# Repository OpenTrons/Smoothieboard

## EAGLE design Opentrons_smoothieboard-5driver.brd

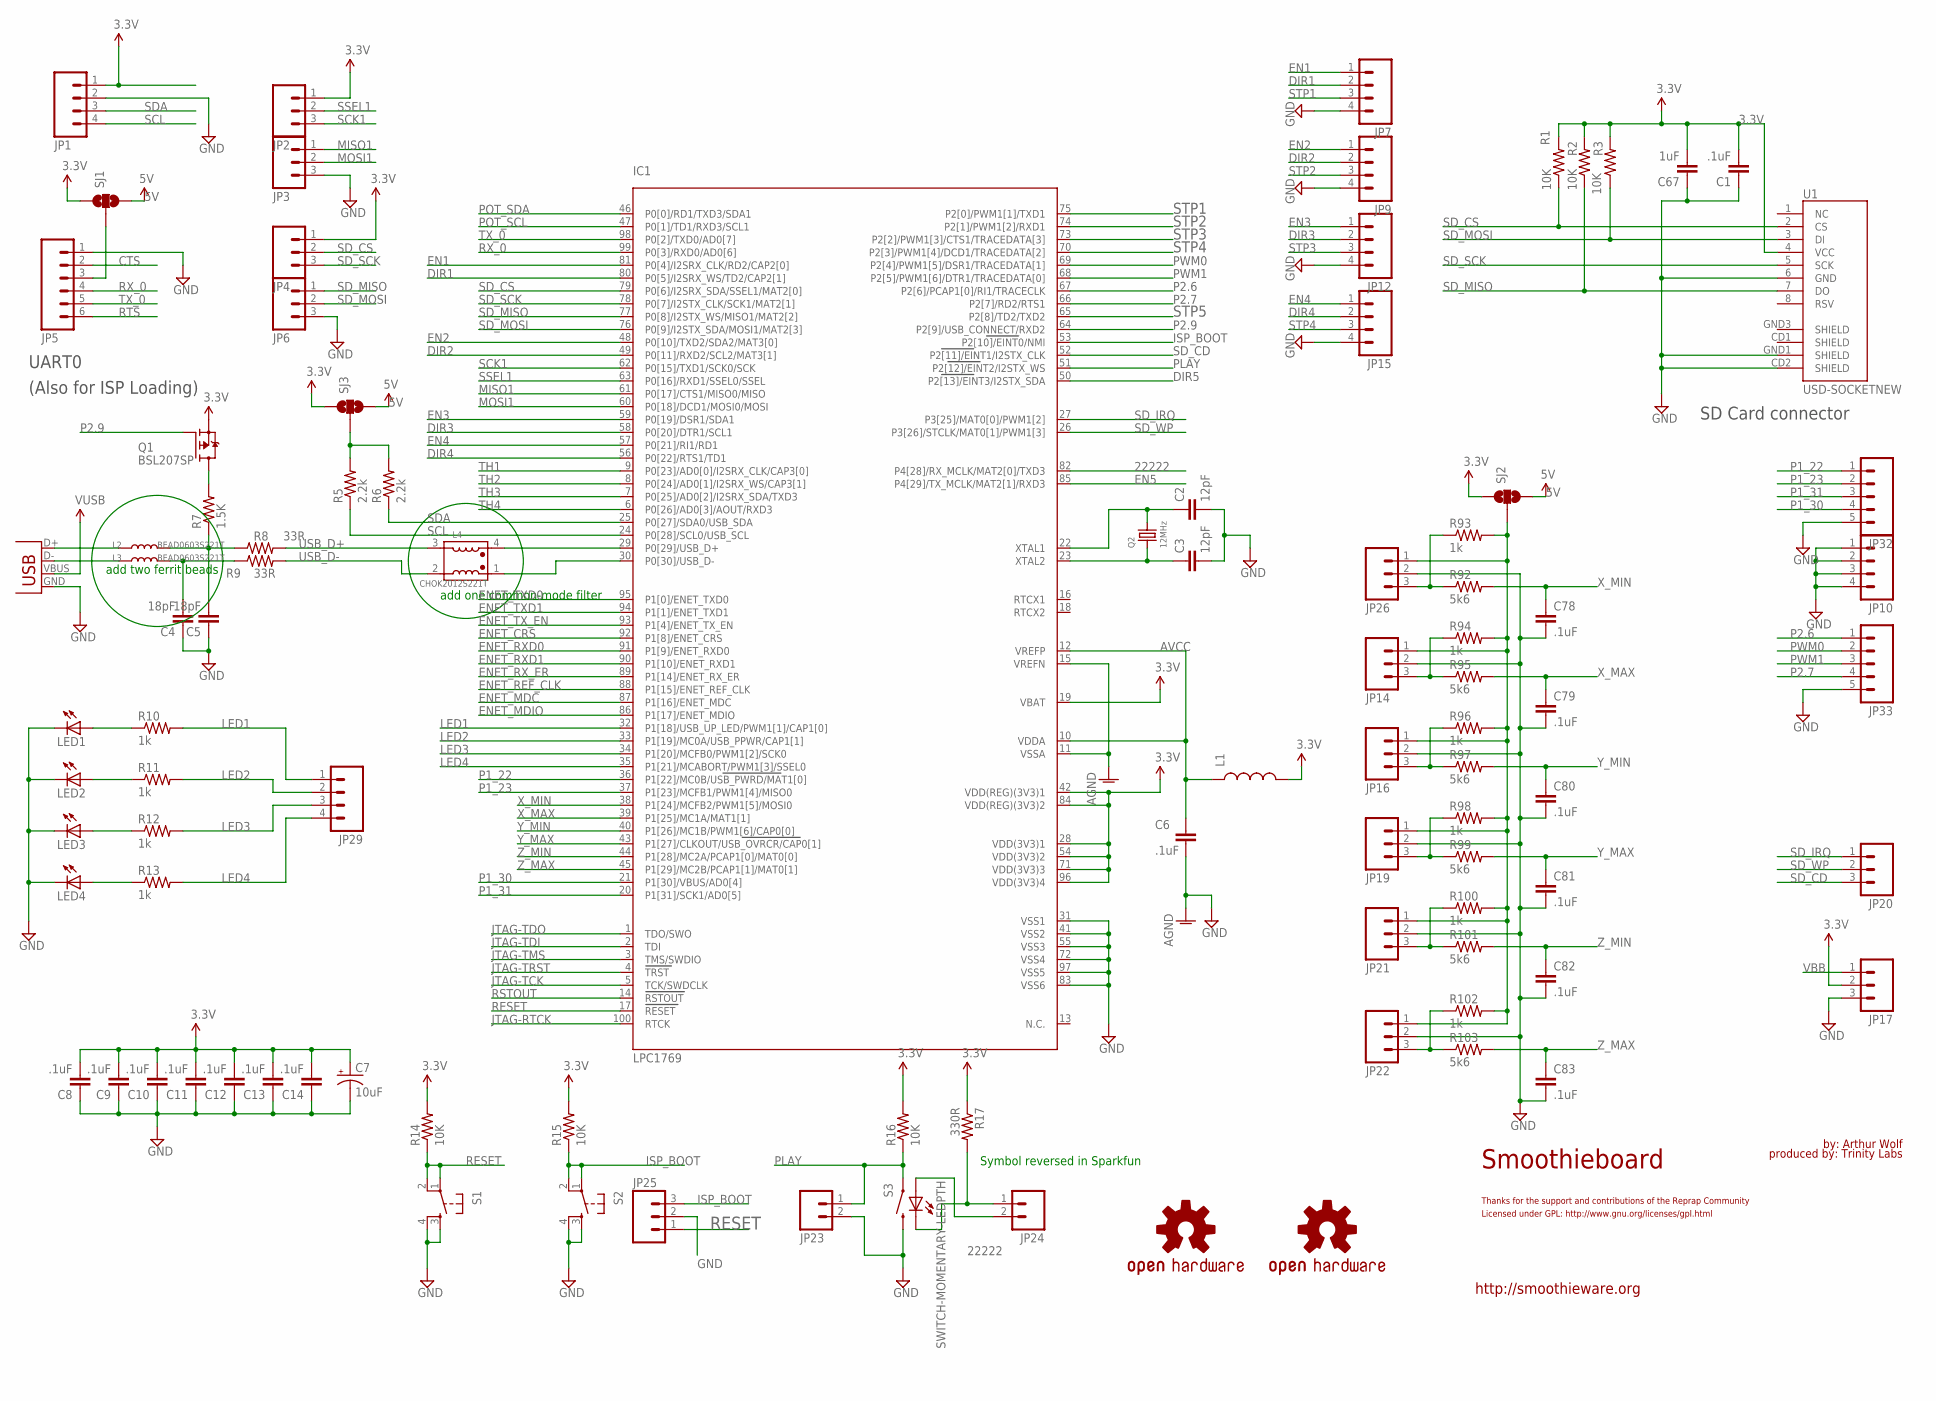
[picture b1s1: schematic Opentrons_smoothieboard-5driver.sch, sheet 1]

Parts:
C1, C6, C8, C9, C10, C11, C12, C13, C14, C78, C79, C80, C81, C82, C83: .1uF; C0603
C2, C3: 12pF; C0603
C4, C5: 18pF; C0603
C7: 10uF; EIA3216
C67: 1uF; C0805
IC1: LPC1769; LQFP100
JP1, JP7, JP9, JP10, JP12, JP15, JP29: M041X04_NO_SILK; 1X04_NO_SILK
JP2, JP3, JP4, JP6: M031X03_NO_SILK; 1X03_NO_SILK
JP5: M06POLAR; MOLEX-1X6
JP14, JP16, JP19, JP21, JP22, JP26: M03POLAR; MOLEX-1X3
JP17, JP20, JP25: M03PTH; 1X03
JP23, JP24: M02PTH; 1X02
JP32, JP33: M05PTH; 1X05
L1: INDUCTOR0603; 0603
L2, L3: BEAD0603S221T; 0603(1608)
L4: CHOK2012S221T; L-2012
LED1, LED2, LED3, LED4: LEDCHIP-LED0805; CHIP-LED0805
Q1: BSL207SP; SC74_INFINEON
Q2: 12MHz; CRYSTAL_3.2X2.5
R1, R2, R3, R14, R15, R16: 10K; R0603
R5, R6: 2.2k; R0603
R7: 1.5K; R0603
R8, R9: 33R; R0603
R10, R11, R12, R13, R93, R94, R96, R98, R100, R102: 1k; R0603
R17: 330R; R0603
R92, R95, R97, R99, R101, R103: 5k6; R0603
S1, S2: TAC_SWITCHSMD; TACTILE_SWITCH_SMD
S3: SWITCH-MOMENTARY-LEDPTH; TACTILE-PTH-LED-12MM
SJ1, SJ2, SJ3: SOLDERJUMPER_2WAYS; SJ_3
U1: USD-SOCKETNEW; MICRO-SD-SOCKET-PP
U$8, U$9: OSHW-LOGOH; OSHW-LOGO-HUGE
X14: USBPTH; USB-B-PTH

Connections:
3.3V: C1.2, C7.A (+), C8.2, C9.2, C10.2, C11.2, C12.2, C13.2, C14.2, C67.2, IC1.19 (VBAT), IC1.28 (VDD(3V3)1), IC1.42 (VDD(REG)(3V3)1), IC1.54 (VDD(3V3)2), IC1.71 (VDD(3V3)3), IC1.84 (VDD(REG)(3V3)2), IC1.96 (VDD(3V3)4), JP1.1, JP2.1, JP4.1, JP17.2, L1.2, Q1.4 (S), R1.2, R2.2, R3.2, R14.2, R15.2, R16.2, R17.1, SJ1.1, SJ2.1, SJ3.1, U1.4 (VCC); also elsewhere on the board
5V: SJ1.3, SJ2.3, SJ3.3; also elsewhere on the board
22222: IC1.82 (P4[28]/RX_MCLK/MAT2[0]/TXD3), JP24.2, S3.A
AGND: C6.2, IC1.11 (VSSA), IC1.15 (VREFN); also elsewhere on the board
AVCC: C6.1, IC1.10 (VDDA), IC1.12 (VREFP), L1.1; also elsewhere on the board
CTS: JP5.2
DIR1: IC1.80 (P0[5]/I2SRX_WS/TD2/CAP2[1]), JP7.2; also elsewhere on the board
DIR2: IC1.49 (P0[11]/RXD2/SCL2/MAT3[1]), JP9.2; also elsewhere on the board
DIR3: IC1.58 (P0[20]/DTR1/SCL1), JP12.2; also elsewhere on the board
DIR4: IC1.56 (P0[22]/RTS1/TD1), JP15.2; also elsewhere on the board
DIR5: IC1.50 (P2[13]/EINT3/I2STX_SDA); also elsewhere on the board
EN1: IC1.81 (P0[4]/I2SRX_CLK/RD2/CAP2[0]), JP7.1; also elsewhere on the board
EN2: IC1.48 (P0[10]/TXD2/SDA2/MAT3[0]), JP9.1; also elsewhere on the board
EN3: IC1.59 (P0[19]/DSR1/SDA1), JP12.1; also elsewhere on the board
EN4: IC1.57 (P0[21]/RI1/RD1), JP15.1; also elsewhere on the board
EN5: IC1.85 (P4[29]/TX_MCLK/MAT2[1]/RXD3); also elsewhere on the board
ENET_CRS: IC1.92 (P1[8]/ENET_CRS); also elsewhere on the board
ENET_MDC: IC1.87 (P1[16]/ENET_MDC); also elsewhere on the board
ENET_MDIO: IC1.86 (P1[17]/ENET_MDIO); also elsewhere on the board
ENET_REF_CLK: IC1.88 (P1[15]/ENET_REF_CLK); also elsewhere on the board
ENET_RXD0: IC1.91 (P1[9]/ENET_RXD0); also elsewhere on the board
ENET_RXD1: IC1.90 (P1[10]/ENET_RXD1); also elsewhere on the board
ENET_RX_ER: IC1.89 (P1[14]/ENET_RX_ER); also elsewhere on the board
ENET_TXD0: IC1.95 (P1[0]/ENET_TXD0); also elsewhere on the board
ENET_TXD1: IC1.94 (P1[1]/ENET_TXD1); also elsewhere on the board
ENET_TX_EN: IC1.93 (P1[4]/ENET_TX_EN); also elsewhere on the board
GND: C1.1, C2.2, C3.2, C4.1, C5.1, C7.C (-), C8.1, C9.1, C10.1, C11.1, C12.1, C13.1, C14.1, C67.1, C78.2, C79.2, C80.2, C81.2, C82.2, C83.2, IC1.31 (VSS1), IC1.41 (VSS2), IC1.55 (VSS3), IC1.72 (VSS4), IC1.83 (VSS6), IC1.97 (VSS5), JP1.2, JP3.3, JP5.1, JP6.3, JP7.4, JP9.4, JP10.1, JP10.2, JP10.3, JP10.4, JP12.4, JP14.2, JP15.4, JP16.2, JP17.3, JP19.2, JP21.2, JP22.2, JP23.2, JP25.2, JP26.2, JP32.5, JP33.5, LED1.C, LED2.C, LED3.C, LED4.C, S1.3, S1.4, S2.3, S2.4, S3.2, U1.6 (GND), U1.CD2 (SHIELD), U1.GND1 (SHIELD), X14.GND; also elsewhere on the board
ISP_BOOT: IC1.53 (P2[10]/EINT0/NMI), JP25.3, R15.1, S2.1, S2.2
JTAG-RTCK: IC1.100 (RTCK)
JTAG-TCK: IC1.5 (TCK/SWDCLK)
JTAG-TDI: IC1.2 (TDI)
JTAG-TDO: IC1.1 (TDO/SWO)
JTAG-TMS: IC1.3 (TMS/SWDIO)
JTAG-TRST: IC1.4 (TRST)
LED1: IC1.32 (P1[18]/USB_UP_LED/PWM1[1]/CAP1[0]), JP29.1, R10.2
LED2: IC1.33 (P1[19]/MC0A/USB_PPWR/CAP1[1]), JP29.2, R11.2
LED3: IC1.34 (P1[20]/MCFB0/PWM1[2]/SCK0), JP29.3, R12.2
LED4: IC1.35 (P1[21]/MCABORT/PWM1[3]/SSEL0), JP29.4, R13.2
MISO1: IC1.61 (P0[17]/CTS1/MISO0/MISO), JP3.1
MOSI1: IC1.60 (P0[18]/DCD1/MOSI0/MOSI), JP3.2
unnamed: C2.1, IC1.22 (XTAL1), Q2.2
unnamed: C3.1, IC1.23 (XTAL2), Q2.1
unnamed: JP5.3, SJ1.2
unnamed: Q1.1 (D), Q1.2 (D), Q1.5 (D), Q1.6 (D), R7.2
unnamed: L2.1, X14.D+
unnamed: L3.1, X14.D-
unnamed: JP24.1, R17.2, S3.C
unnamed: LED4.A, R13.1
unnamed: LED3.A, R12.1
unnamed: LED2.A, R11.1
unnamed: LED1.A, R10.1
unnamed: JP14.3, R94.1, R95.1
unnamed: JP14.1, JP16.1, JP19.1, JP21.1, JP22.1, JP26.1, R93.2, R94.2, R96.2, R98.2, R100.2, R102.2, SJ2.2
unnamed: JP16.3, R96.1, R97.1
unnamed: JP19.3, R98.1, R99.1
unnamed: JP22.3, R102.1, R103.1
unnamed: JP21.3, R100.1, R101.1
unnamed: JP26.3, R92.1, R93.1
unnamed: R5.2, R6.2, SJ3.2
unnamed: C5.2, L2.2, R7.1, R8.1
unnamed: C4.2, L3.2, R9.1
unnamed: IC1.30 (P0[30]/USB_D-), L4.1
unnamed: IC1.29 (P0[29]/USB_D+), L4.4
P1_22: IC1.36 (P1[22]/MC0B/USB_PWRD/MAT1[0]), JP32.1; also elsewhere on the board
P1_23: IC1.37 (P1[23]/MCFB1/PWM1[4]/MISO0), JP32.2; also elsewhere on the board
P1_30: IC1.21 (P1[30]/VBUS/AD0[4]), JP32.4
P1_31: IC1.20 (P1[31]/SCK1/AD0[5]), JP32.3
P2.6: IC1.67 (P2[6]/PCAP1[0]/RI1/TRACECLK), JP33.1; also elsewhere on the board
P2.7: IC1.66 (P2[7]/RD2/RTS1), JP33.4; also elsewhere on the board
P2.9: IC1.64 (P2[9]/USB_CONNECT/RXD2), Q1.3 (G)
PLAY: IC1.51 (P2[12]/EINT2/I2STX_WS), JP23.1, R16.1, S3.4 (1)
POT_SCL: IC1.47 (P0[1]/TD1/RXD3/SCL1); also elsewhere on the board
POT_SDA: IC1.46 (P0[0]/RD1/TXD3/SDA1); also elsewhere on the board
PWM0: IC1.69 (P2[4]/PWM1[5]/DSR1/TRACEDATA[1]), JP33.2; also elsewhere on the board
PWM1: IC1.68 (P2[5]/PWM1[6]/DTR1/TRACEDATA[0]), JP33.3; also elsewhere on the board
RESET: IC1.17 (RESET), JP25.1, R14.1, S1.1, S1.2
RSTOUT: IC1.14 (RSTOUT); also elsewhere on the board
RTS: JP5.6
RX_0: IC1.99 (P0[3]/RXD0/AD0[6]), JP5.4
SCK1: IC1.62 (P0[15]/TXD1/SCK0/SCK), JP2.3
SCL: IC1.24 (P0[28]/SCL0/USB_SCL), JP1.4, R5.1
SDA: IC1.25 (P0[27]/SDA0/USB_SDA), JP1.3, R6.1
SD_CD: IC1.52 (P2[11]/EINT1/I2STX_CLK), JP20.3
SD_CS: IC1.79 (P0[6]/I2SRX_SDA/SSEL1/MAT2[0]), JP4.2, R1.1, U1.2 (CS)
SD_IRQ: IC1.27 (P3[25]/MAT0[0]/PWM1[2]), JP20.1
SD_MISO: IC1.77 (P0[8]/I2STX_WS/MISO1/MAT2[2]), JP6.1, R2.1, U1.7 (DO)
SD_MOSI: IC1.76 (P0[9]/I2STX_SDA/MOSI1/MAT2[3]), JP6.2, R3.1, U1.3 (DI)
SD_SCK: IC1.78 (P0[7]/I2STX_CLK/SCK1/MAT2[1]), JP4.3, U1.5 (SCK)
SD_WP: IC1.26 (P3[26]/STCLK/MAT0[1]/PWM1[3]), JP20.2
SSEL1: IC1.63 (P0[16]/RXD1/SSEL0/SSEL), JP2.2
STP1: IC1.75 (P2[0]/PWM1[1]/TXD1), JP7.3; also elsewhere on the board
STP2: IC1.74 (P2[1]/PWM1[2]/RXD1), JP9.3; also elsewhere on the board
STP3: IC1.73 (P2[2]/PWM1[3]/CTS1/TRACEDATA[3]), JP12.3; also elsewhere on the board
STP4: IC1.70 (P2[3]/PWM1[4]/DCD1/TRACEDATA[2]), JP15.3; also elsewhere on the board
STP5: IC1.65 (P2[8]/TD2/TXD2); also elsewhere on the board
TH1: IC1.9 (P0[23]/AD0[0]/I2SRX_CLK/CAP3[0]); also elsewhere on the board
TH2: IC1.8 (P0[24]/AD0[1]/I2SRX_WS/CAP3[1]); also elsewhere on the board
TH3: IC1.7 (P0[25]/AD0[2]/I2SRX_SDA/TXD3); also elsewhere on the board
TH4: IC1.6 (P0[26]/AD0[3]/AOUT/RXD3); also elsewhere on the board
TX_0: IC1.98 (P0[2]/TXD0/AD0[7]), JP5.5
USB_D+: L4.3, R8.2
USB_D-: L4.2, R9.2
VBB: JP17.1; also elsewhere on the board
VUSB: X14.VBUS; also elsewhere on the board
X_MAX: C79.1, IC1.39 (P1[25]/MC1A/MAT1[1]), R95.2
X_MIN: C78.1, IC1.38 (P1[24]/MCFB2/PWM1[5]/MOSI0), R92.2
Y_MAX: C81.1, IC1.43 (P1[27]/CLKOUT/USB_OVRCR/CAP0[1]), R99.2
Y_MIN: C80.1, IC1.40 (P1[26]/MC1B/PWM1[6]/CAP0[0]), R97.2
Z_MAX: C83.1, IC1.45 (P1[29]/MC2B/PCAP1[1]/MAT0[1]), R103.2
Z_MIN: C82.1, IC1.44 (P1[28]/MC2A/PCAP1[0]/MAT0[0]), R101.2

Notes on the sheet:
SD Card connector
UART0
(Also for ISP Loading)
http://smoothieware.org
Symbol reversed in Sparkfun
Smoothieboard
by: Arthur Wolf
produced by: Trinity Labs
Licensed under GPL: http://www.gnu.org/licenses/gpl.html
Thanks for the support and contributions of the Reprap Community
add two ferrit beads
add one common-mode filter

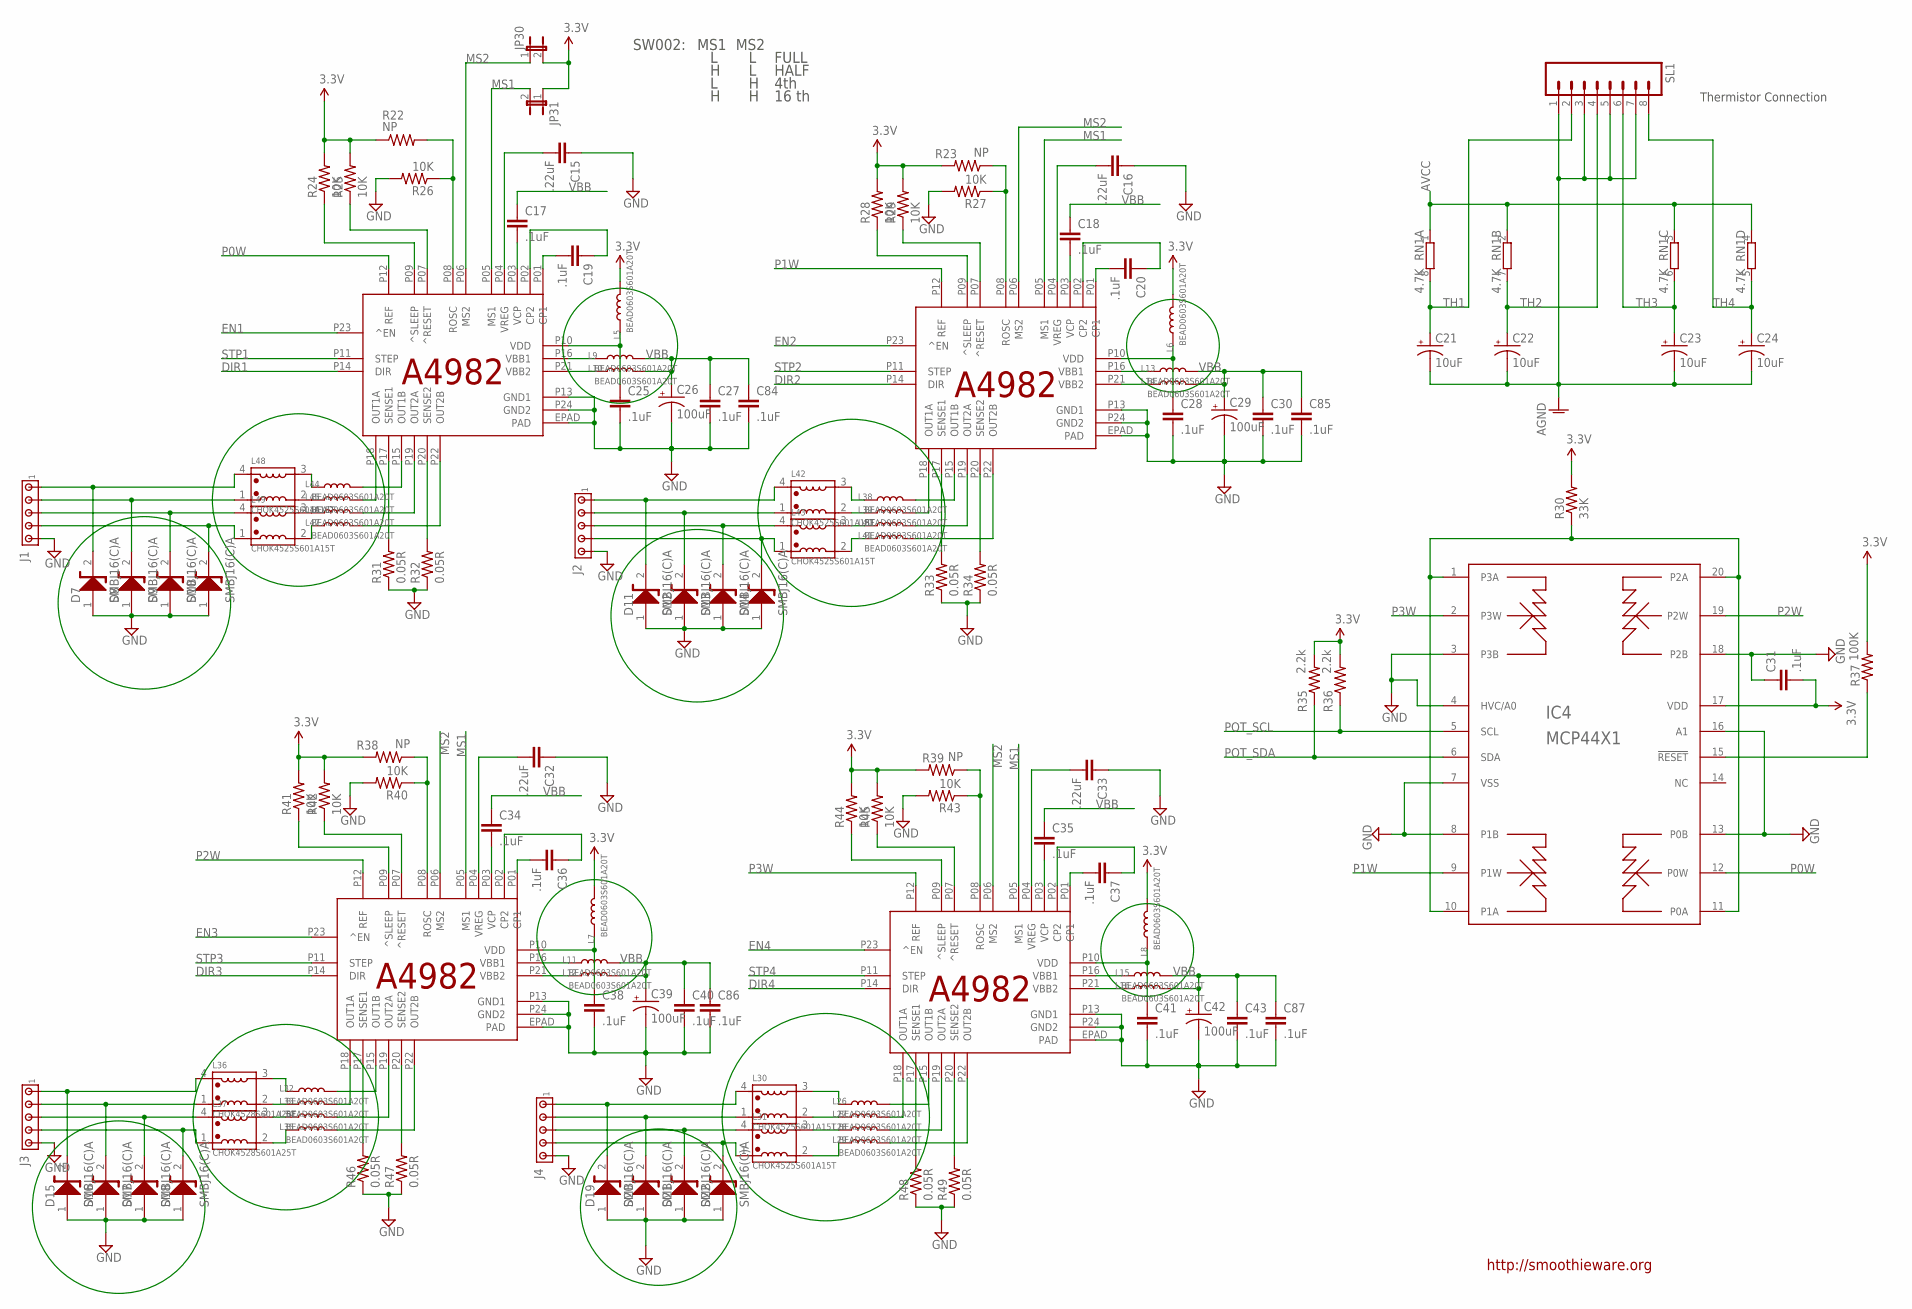
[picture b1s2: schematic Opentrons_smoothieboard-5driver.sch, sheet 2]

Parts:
C15, C16, C32, C33: .22uF; C0603
C17, C18, C19, C20, C25, C27, C28, C30, C31, C34, C35, C36, C37, C38, C40, C41, C43, C84, C85, C86, C87: .1uF; C0603
C21, C22, C23, C24: 10uF; EIA3216
C26, C29, C39, C42: 100uF; PANASONIC_E
D7, D8, D9, D10, D11, D12, D13, D14, D15, D16, D17, D18, D19, D20, D21, D22: SMBJ16(C)A; DO214-AA_(SMB)
IC2, IC3, IC5, IC6: A4982; ETSSOP24
IC4: MCP44X1; TSSOP20
J1, J2, J3, J4: MTA05-100; 10X05MTA
JP30, JP31: JUMPER-2SMD-NC; SJ_2S
L5, L6, L7, L8, L9, L10, L11, L12, L13, L14, L15, L16, L26, L27, L28, L29, L32, L33, L34, L35, L38, L39, L40, L41, L44, L45, L46, L47: BEAD0603S601A20T; 0603(1608)
L30, L31, L42, L43, L48, L49: CHOK4525S601A15T; L-4525
L36, L37: CHOK4528S601A25T; L-4528
R22, R23, R38, R39: NP; R0603
R24, R25, R26, R27, R28, R29, R40, R41, R42, R43, R44, R45: 10K; R0603
R30: 33K; R0603
R31, R32, R33, R34, R46, R47, R48, R49: 0.05R; R2512
R35, R36: 2.2k; R0603
R37: 100K; R0603
RN1: 4.7K; 0603-ARV
SL1: M08; 08P

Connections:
3.3V: C31.2, IC4.17 (VDD), JP30.2, JP31.1, L5.2, L6.2, L7.2, L8.2, R22.1, R23.2, R24.2, R25.2, R28.2, R29.2, R30.2, R35.2, R36.2, R37.2, R38.2, R39.2, R41.2, R42.2, R44.2, R45.2; also elsewhere on the board
AGND: C21.C (-), C22.C (-), C23.C (-), C24.C (-), SL1.1, SL1.3, SL1.5, SL1.7; also elsewhere on the board
AVCC: RN1.1, RN1.2 (1), RN1.3 (1), RN1.4 (1); also elsewhere on the board
DIR1: IC2.P14 (DIR); also elsewhere on the board
DIR2: IC3.P14 (DIR); also elsewhere on the board
DIR3: IC5.P14 (DIR); also elsewhere on the board
DIR4: IC6.P14 (DIR); also elsewhere on the board
EN1: IC2.P23 (^EN); also elsewhere on the board
EN2: IC3.P23 (^EN); also elsewhere on the board
EN3: IC5.P23 (^EN); also elsewhere on the board
EN4: IC6.P23 (^EN); also elsewhere on the board
GND: C15.1, C16.1, C25.2, C26.-, C27.2, C28.2, C29.-, C30.2, C31.1, C32.1, C33.1, C38.2, C39.-, C40.2, C41.2, C42.-, C43.2, C84.2, C85.2, C86.2, C87.2, D7.1 (A), D8.1 (A), D9.1 (A), D10.1 (A), D11.1 (A), D12.1 (A), D13.1 (A), D14.1 (A), D15.1 (A), D16.1 (A), D17.1 (A), D18.1 (A), D19.1 (A), D20.1 (A), D21.1 (A), D22.1 (A), IC2.EPAD (PAD), IC2.P13 (GND1), IC2.P24 (GND2), IC3.EPAD (PAD), IC3.P13 (GND1), IC3.P24 (GND2), IC4.3 (P3B), IC4.4 (HVC/A0), IC4.7 (VSS), IC4.8 (P1B), IC4.13 (P0B), IC4.16 (A1), IC4.18 (P2B), IC5.EPAD (PAD), IC5.P13 (GND1), IC5.P24 (GND2), IC6.EPAD (PAD), IC6.P13 (GND1), IC6.P24 (GND2), J1.5, J2.5, J3.5, J4.5, R26.2, R27.2, R31.1, R32.1, R33.1, R34.1, R40.2, R43.2, R46.1, R47.1, R48.1, R49.1; also elsewhere on the board
J1_1A: D7.2 (K), J1.1, L48.4
J1_1B: D8.2 (K), J1.2, L48.1
J1_2A: D9.2 (K), J1.3, L49.4
J1_2B: D10.2 (K), J1.4, L49.1
J2_1A: D11.2 (K), J2.1, L42.4
J2_1B: D12.2 (K), J2.2, L42.1
J2_2A: D13.2 (K), J2.3, L43.4
J2_2B: D14.2 (K), J2.4, L43.1
J3_1A: D15.2 (K), J3.1, L36.4
J3_1B: D16.2 (K), J3.2, L36.1
J3_2A: D17.2 (K), J3.3, L37.4
J3_2B: D18.2 (K), J3.4, L37.1
J4_1A: D19.2 (K), J4.1, L30.4
J4_1B: D20.2 (K), J4.2, L30.1
J4_2A: D21.2 (K), J4.3, L31.4
J4_2B: D22.2 (K), J4.4, L31.1
MS1: IC2.P05 (MS1), IC3.P05 (MS1), IC5.P05 (MS1), IC6.P05 (MS1), JP31.2; also elsewhere on the board
MS2: IC2.P06 (MS2), IC3.P06 (MS2), IC5.P06 (MS2), IC6.P06 (MS2), JP30.1; also elsewhere on the board
unnamed: C20.2, IC3.P01 (CP1)
unnamed: C20.1, IC3.P02 (CP2)
unnamed: IC2.P07 (^RESET), R25.1
unnamed: C18.2, IC3.P03 (VCP)
unnamed: IC3.P17 (SENSE1), R33.2
unnamed: IC3.P20 (SENSE2), R34.2
unnamed: IC3.P18 (OUT1A), L39.2
unnamed: IC3.P19 (OUT2A), L40.2
unnamed: IC4.15 (!RESET), R37.1
unnamed: IC3.P22 (OUT2B), L41.2
unnamed: IC4.1 (P3A), IC4.10 (P1A), IC4.11 (P0A), IC4.20 (P2A), R30.1
unnamed: IC3.P08 (ROSC), R23.1, R27.1
unnamed: C16.2, IC3.P04 (VREG)
unnamed: IC3.P09 (^SLEEP), R28.1
unnamed: C36.2, IC5.P01 (CP1)
unnamed: C36.1, IC5.P02 (CP2)
unnamed: C34.2, IC5.P03 (VCP)
unnamed: IC5.P17 (SENSE1), R46.2
unnamed: IC5.P20 (SENSE2), R47.2
unnamed: IC5.P18 (OUT1A), L33.2
unnamed: IC5.P15 (OUT1B), L32.2
unnamed: IC5.P19 (OUT2A), L34.2
unnamed: IC5.P22 (OUT2B), L35.2
unnamed: IC3.P07 (^RESET), R29.1
unnamed: IC5.P07 (^RESET), R42.1
unnamed: IC5.P08 (ROSC), R38.1, R40.1
unnamed: C32.2, IC5.P04 (VREG)
unnamed: IC6.P07 (^RESET), R45.1
unnamed: IC5.P09 (^SLEEP), R41.1
unnamed: C37.2, IC6.P01 (CP1)
unnamed: C37.1, IC6.P02 (CP2)
unnamed: C35.2, IC6.P03 (VCP)
unnamed: IC6.P17 (SENSE1), R48.2
unnamed: IC6.P20 (SENSE2), R49.2
unnamed: IC6.P15 (OUT1B), L26.2
unnamed: IC6.P19 (OUT2A), L28.2
unnamed: IC6.P22 (OUT2B), L29.2
unnamed: IC6.P08 (ROSC), R39.1, R43.1
unnamed: C33.2, IC6.P04 (VREG)
unnamed: IC6.P09 (^SLEEP), R44.1
unnamed: IC6.P18 (OUT1A), L27.2
unnamed: C19.2, IC2.P01 (CP1)
unnamed: C19.1, IC2.P02 (CP2)
unnamed: C17.2, IC2.P03 (VCP)
unnamed: IC2.P17 (SENSE1), R31.2
unnamed: IC2.P20 (SENSE2), R32.2
unnamed: IC2.P18 (OUT1A), L45.2
unnamed: IC2.P15 (OUT1B), L44.2
unnamed: IC2.P19 (OUT2A), L46.2
unnamed: IC2.P22 (OUT2B), L47.2
unnamed: IC2.P08 (ROSC), R22.2, R26.1
unnamed: C15.2, IC2.P04 (VREG)
unnamed: IC2.P09 (^SLEEP), R24.1
unnamed: C25.1, IC2.P10 (VDD), L5.1
unnamed: C38.1, IC5.P10 (VDD), L7.1
unnamed: C28.1, IC3.P10 (VDD), L6.1
unnamed: C41.1, IC6.P10 (VDD), L8.1
unnamed: IC2.P16 (VBB1), L9.1
unnamed: IC2.P21 (VBB2), L10.1
unnamed: IC3.P16 (VBB1), L13.1
unnamed: IC3.P21 (VBB2), L14.1
unnamed: IC5.P16 (VBB1), L11.1
unnamed: IC5.P21 (VBB2), L12.1
unnamed: IC6.P16 (VBB1), L15.1
unnamed: IC6.P21 (VBB2), L16.1
unnamed: L26.1, L30.3
unnamed: L27.1, L30.2
unnamed: L28.1, L31.3
unnamed: L29.1, L31.2
unnamed: L33.1, L36.2
unnamed: L34.1, L37.3
unnamed: L32.1, L36.3
unnamed: L35.1, L37.2
unnamed: IC3.P15 (OUT1B), L38.2
unnamed: L40.1, L43.3
unnamed: L39.1, L42.2
unnamed: L41.1, L43.2
unnamed: L38.1, L42.3
unnamed: L45.1, L48.2
unnamed: L46.1, L49.3
unnamed: L44.1, L48.3
unnamed: L47.1, L49.2
P0W: IC2.P12 (REF), IC4.12 (P0W)
P1W: IC3.P12 (REF), IC4.9 (P1W)
P2W: IC4.19 (P2W), IC5.P12 (REF)
P3W: IC4.2 (P3W), IC6.P12 (REF)
POT_SCL: IC4.5 (SCL), R36.1; also elsewhere on the board
POT_SDA: IC4.6 (SDA), R35.1; also elsewhere on the board
STP1: IC2.P11 (STEP); also elsewhere on the board
STP2: IC3.P11 (STEP); also elsewhere on the board
STP3: IC5.P11 (STEP); also elsewhere on the board
STP4: IC6.P11 (STEP); also elsewhere on the board
TH1: C21.A (+), RN1.8 (2), SL1.2; also elsewhere on the board
TH2: C22.A (+), RN1.7 (2), SL1.4; also elsewhere on the board
TH3: C23.A (+), RN1.6 (2), SL1.6; also elsewhere on the board
TH4: C24.A (+), RN1.5 (2), SL1.8; also elsewhere on the board
VBB: C17.1, C18.1, C26.+, C27.1, C29.+, C30.1, C34.1, C35.1, C39.+, C40.1, C42.+, C43.1, C84.1, C85.1, C86.1, C87.1, L9.2, L10.2, L11.2, L12.2, L13.2, L14.2, L15.2, L16.2; also elsewhere on the board

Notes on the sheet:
SW002:
MS1
MS2
FULL
HALF
4th
16 th
Thermistor Connection
http://smoothieware.org

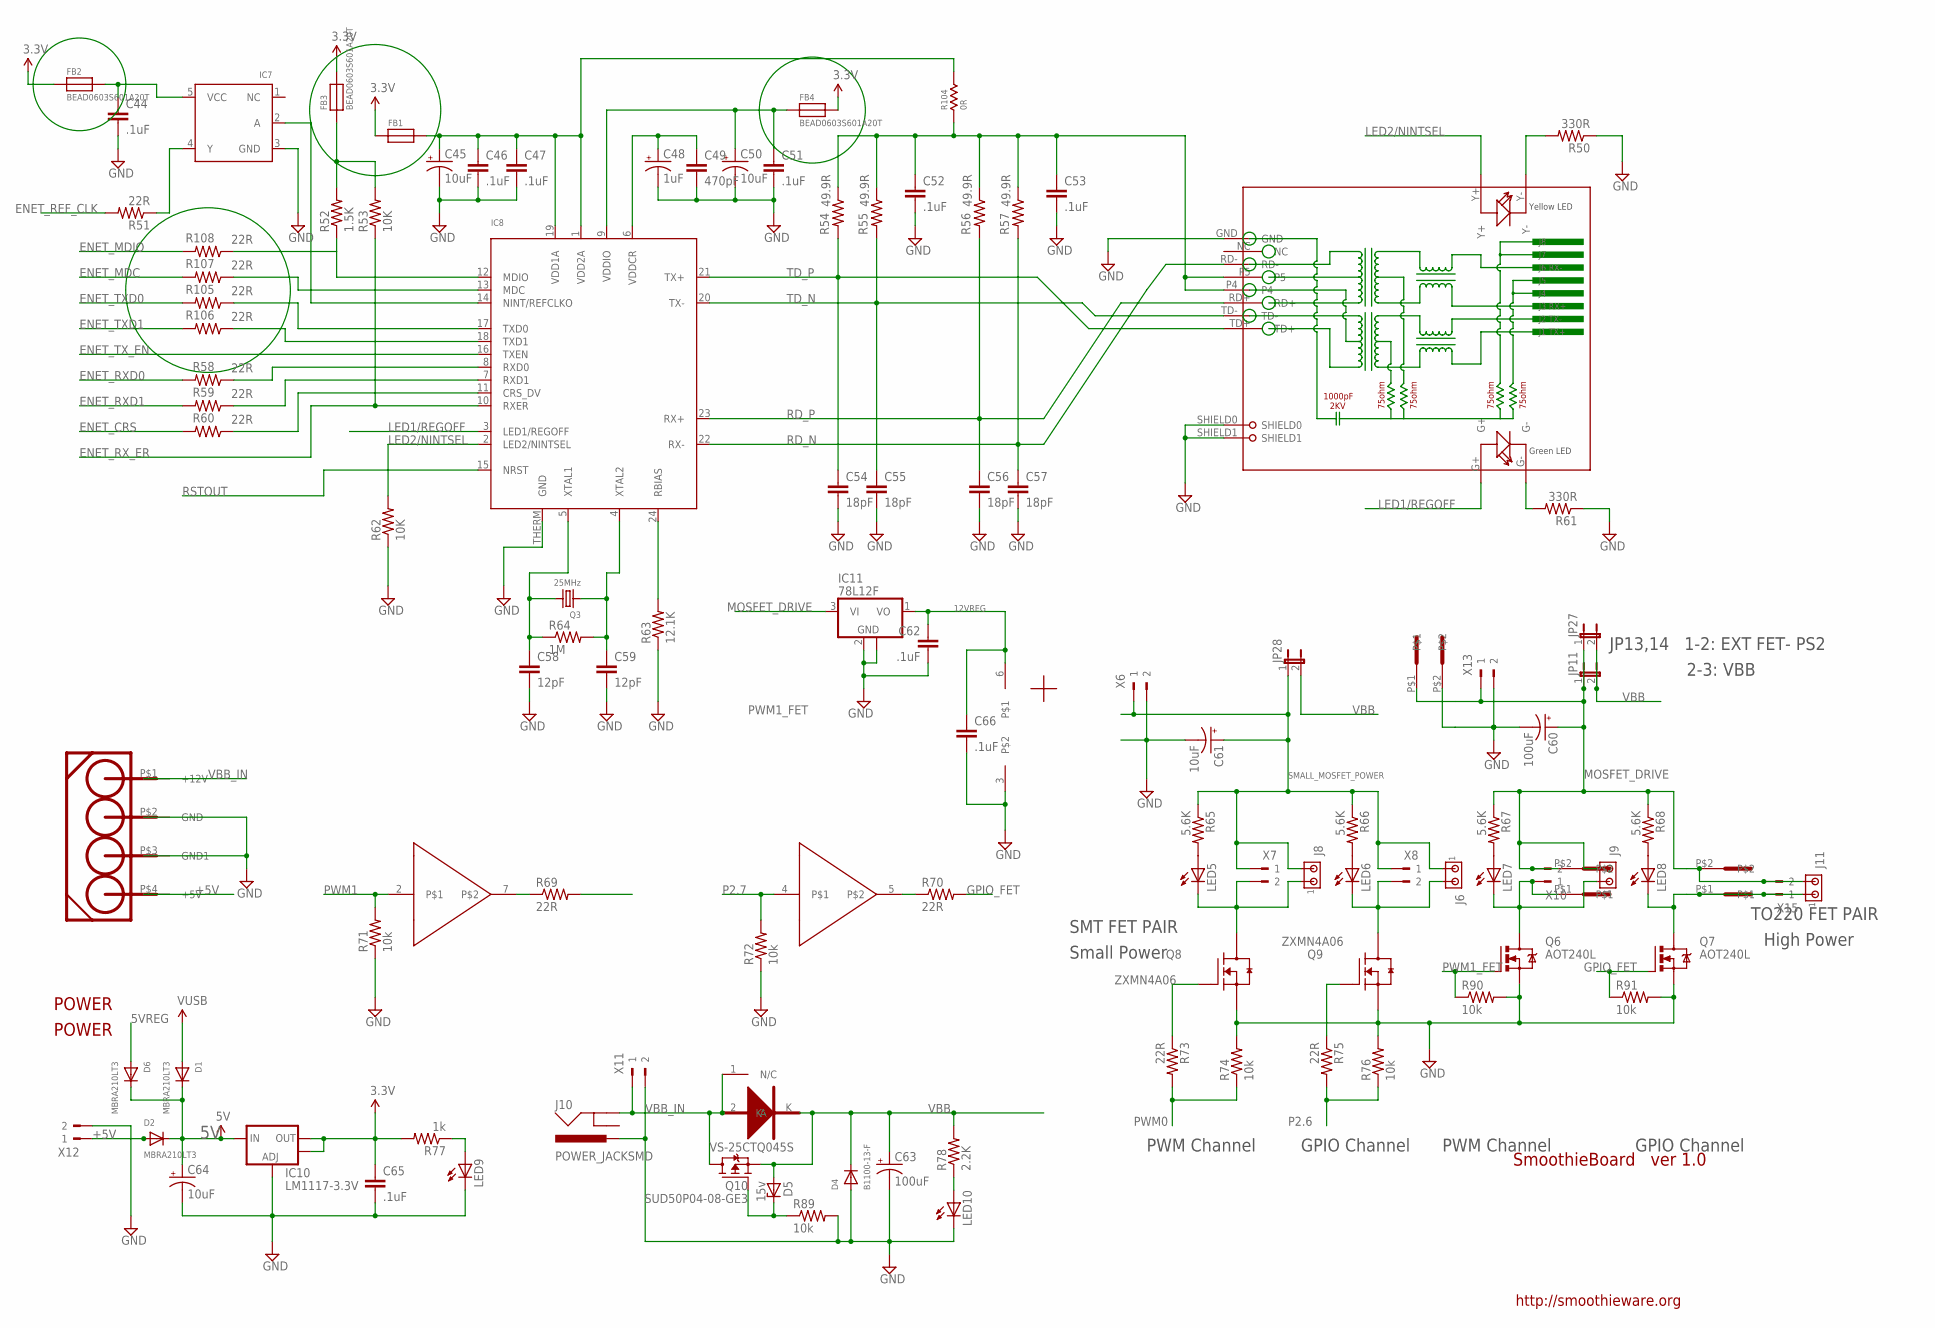
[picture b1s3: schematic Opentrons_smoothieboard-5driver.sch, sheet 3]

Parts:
C44, C46, C47, C51, C52, C53, C62, C65, C66: .1uF; C0603
C45, C50, C61, C64: 10uF; EIA3216
C48: 1uF; EIA3216
C49: 470pF; C0603K
C54, C55, C56, C57: 18pF; C0603
C58, C59: 12pF; C0603
C60: 100uF; PANASONIC_E
C63: 100uF; PANASONIC_D
D1, D2, D6: MBRA210LT3; SMADIODE
D3: VS-25CTQ045S; TO263AB
D4: B1100-13-F; SMADIODE
D5: 15v; SMB
FB1: FERRITE; 0603
FB2, FB3, FB4: BEAD0603S601A20T; 0603
IC7: 74LVC1G04; SOT23-5
IC8: LAN8720; QFN24_4MM
IC10: LM1117-3.3V; SOT223
IC11: 78L12F; SOT89
IC14: TC4427; SOIC8
J6, J8, J9, J11: MTA02-100; 10X02MTA
J10: POWER_JACKSMD; POWER_JACK_SMD
JP11, JP27, JP28: JP1E; JP1
LED5, LED6, LED7, LED8, LED9, LED10: LEDCHIP-LED0805; CHIP-LED0805
POWER: POWER; MOLEX8981
Q3: 25MHz; CRYSTAL_3.2X2.5
Q6, Q7: AOT240L; TO220BV
Q8, Q9: ZXMN4A06; SOT230P700X160-4N
Q10: SUD50P04-08-GE3; TO252
R50, R61: 330R; R0603
R51, R58, R59, R60, R69, R70, R73, R75, R105, R106, R107, R108: 22R; R0603
R52: 1.5K; R0603
R53, R62: 10K; R0603
R54, R55, R56, R57: 49.9R; R0603
R63: 12.1K; R0603
R64: 1M; R0603
R65, R66, R67, R68: 5.6K; R0603
R71, R72, R74, R76, R89, R90, R91: 10k; R0603
R77: 1k; R0603
R78: 2.2K; R0603
R104: 0R; 0603(1608)
RJ1: HR911105A
U$5, U$6, U$10: 5MMCONN; 1715250000
X6, X7, X8, X10, X11, X12, X13, X15: 180G-2

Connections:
3.3V: C65.1, FB1.1, FB2.1, FB3.2, FB4.2, IC10.2 (OUT), IC10.4 (OUT), R77.2; also elsewhere on the board
5V: C64.A (+), D1.C, D2.C, D6.C, IC10.3 (IN); also elsewhere on the board
5VREG: D6.A; also elsewhere on the board
12VREG: C62.1, C66.1, IC11.1 (VO), IC14.6; also elsewhere on the board
+5V: D2.A, POWER.P$4 (+5V), X12.1
ENET_CRS: R60.2; also elsewhere on the board
ENET_MDC: R107.2; also elsewhere on the board
ENET_MDIO: R108.2; also elsewhere on the board
ENET_REF_CLK: R51.2; also elsewhere on the board
ENET_RXD0: R58.2; also elsewhere on the board
ENET_RXD1: R59.2; also elsewhere on the board
ENET_RX_ER: IC8.10 (RXER), R53.1; also elsewhere on the board
ENET_TXD0: R105.2; also elsewhere on the board
ENET_TXD1: R106.2; also elsewhere on the board
ENET_TX_EN: IC8.16 (TXEN); also elsewhere on the board
GND: C44.2, C45.C (-), C46.2, C47.2, C48.C (-), C49.2, C50.C (-), C51.2, C52.2, C53.2, C54.2, C55.2, C56.2, C57.2, C58.2, C59.2, C60.-, C61.C (-), C62.2, C63.-, C64.C (-), C65.2, C66.2, D4.A, IC7.3 (GND), IC8.THERM (GND), IC10.1 (ADJ), IC11.2 (GND), IC11.2@1 (GND), IC14.3, J10.VIN0 (PWR), LED9.C, LED10.C, POWER.P$2 (GND), POWER.P$3 (GND1), Q6.S, Q7.S, Q8.3 (S), Q9.3 (S), R50.1, R61.1, R62.1, R63.1, R71.1, R72.1, R74.2, R76.2, R89.2, R90.2, R91.2, RJ1.GND, RJ1.SHIELD0, RJ1.SHIELD1, U$5.P$2, X6.2, X11.2, X12.2, X13.2; also elsewhere on the board
GPIO_FET: Q7.G, R70.2, R91.1
LED1/REGOFF: IC8.3 (LED1/REGOFF), RJ1.G+
LED2/NINTSEL: IC8.2 (LED2/NINTSEL), R62.2, RJ1.Y+
MOSFET_DRIVE: C60.+, IC11.3 (VI), J9.2, J11.2, JP11.1, JP27.1, R67.1, R68.1, U$5.P$1, U$6.P$2, U$10.P$2, X10.2, X13.1, X15.2
unnamed: IC14.7, R69.1
unnamed: LED10.A, R78.1
unnamed: J6.2, LED6.C, Q9.4 (D), X8.2
unnamed: IC14.5, R70.1
unnamed: R61.2, RJ1.G-
unnamed: C52.1, C53.1, R54.1, R55.1, R56.1, R57.1, R104.1, RJ1.P4, RJ1.P5
unnamed: IC8.8 (RXD0), R58.1
unnamed: R50.2, RJ1.Y-
unnamed: IC8.7 (RXD1), R59.1
unnamed: IC8.11 (CRS_DV), R60.1
unnamed: C59.1, IC8.4 (XTAL2), Q3.1, R64.2
unnamed: C58.1, IC8.5 (XTAL1), Q3.2, R64.1
unnamed: IC8.24 (RBIAS), R63.2
unnamed: Q8.1 (G), R73.1
unnamed: Q9.1 (G), R75.1
unnamed: IC7.2 (A), IC8.14 (NINT/REFCLKO)
unnamed: IC7.4 (Y), R51.1
unnamed: LED9.A, R77.1
unnamed: LED5.A, R65.2
unnamed: C48.A (+), C49.1, IC8.6 (VDDCR)
unnamed: J8.1, LED5.C, Q8.4 (D), X7.2
unnamed: LED6.A, R66.2
unnamed: J9.1, LED7.C, Q6.D, U$10.P$1, X10.1
unnamed: J11.1, LED8.C, Q7.D, U$6.P$1, X15.1
unnamed: LED7.A, R67.2
unnamed: D5.C, Q10.1 (G), R89.1
unnamed: LED8.A, R68.2
unnamed: C44.1, FB2.2, IC7.5 (VCC)
unnamed: FB3.1, R52.2, R53.2
unnamed: C50.A (+), C51.1, FB4.1, IC8.9 (VDDIO)
unnamed: C45.A (+), C46.1, C47.1, FB1.2, IC8.1 (VDD2A), IC8.19 (VDD1A), R104.2
unnamed: IC8.17 (TXD0), R105.1
unnamed: IC8.18 (TXD1), R106.1
unnamed: IC8.12 (MDIO), R52.1, R108.1
unnamed: IC8.13 (MDC), R107.1
P2.6: R75.2, R76.1; also elsewhere on the board
P2.7: IC14.4, R72.2; also elsewhere on the board
PWM0: R73.2, R74.1; also elsewhere on the board
PWM1: IC14.2, R71.2; also elsewhere on the board
PWM1_FET: Q6.G, R69.2, R90.1
RD_N: C57.1, IC8.22 (RX-), R57.2, RJ1.RD-
RD_P: C56.1, IC8.23 (RX+), R56.2, RJ1.RD+
RSTOUT: IC8.15 (NRST); also elsewhere on the board
SMALL_MOSFET_POWER: C61.A (+), J6.1, J8.2, JP28.1, R65.1, R66.1, X6.1, X7.1, X8.1
TD_N: C55.1, IC8.20 (TX-), R55.2, RJ1.TD-
TD_P: C54.1, IC8.21 (TX+), R54.2, RJ1.TD+
VBB: C63.+, D3.K, D4.C, D5.A, JP11.2, JP27.2, JP28.2, Q10.2 (S), R78.2; also elsewhere on the board
VBB_IN: D3.1 (N/C), D3.2 (A), J10.P$4 (GND), POWER.P$1 (+12V), Q10.3 (D), X11.1
VUSB: D1.A; also elsewhere on the board

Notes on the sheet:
JP13,14 1-2: EXT FET- PS2
2-3: VBB
SMT FET PAIR
Small Power
TO220 FET PAIR
High Power
PWM Channel
GPIO Channel
SmoothieBoard ver 1.0
http://smoothieware.org
VS-25CTQ045S

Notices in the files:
parts and their libraries:
SparkFun-Connectors: Licensing: CC v3.0 Share-Alike You are welcome to use this library for commercial purposes.
